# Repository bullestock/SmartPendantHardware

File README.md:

# Devtronic SmartPendant

This project allows controlling a grblHAL based CNC machine without a PC. It also makes work way more convenient.

This fork builds upon the original Devtronic/Nicolai Shlapunov project, which has a store here: https://devtronic.square.site/

I have no intentions to offer this version for sale, but all files are freely available. The changes compared to the original project are:

* Instead of a display with two FCC connectors this version uses a display with a single 2.54 mm pitch connector. This does mean that the pendant is a few millimetres thicker.
* The LEDs have been removed.
* Passives are 0603 instead of 0805.
* Screw terminals have been replaced with JST XH connectors.

# Firmware

Source code for this project can be found here: **https://github.com/bullestock/SmartPendantFirmware**

To load new firmware you can either use OpenOCD, or the [STM32CubeProgrammer](https://www.st.com/en/development-tools/stm32cubeprog.html).

## OpenOCD

For this you need an "ST-Link V2 mini" adapter, which can be obtained for a few dollars from AliExpress and other sites.

Connect the adapter and run this command:

    openocd -f interface/stlink.cfg -f target/stm32f4x.cfg -c "program SmartPendant.elf verify reset exit"

## STM32CubeProgrammer

Connect SmartPendant to PC using USB-C cable. Press and hold BOOT0 button, then short press NRST button, couple seconds later BOOT0 button can be released.
Open STM32CubeProgrammer. In top right corner choose "USB" from drop down list.
If field "Port" in "USB Configuration" show "No DFU detected" click update button near it.
Click "Connect" button - STM32CubeProgrammer should establish connection and show current device memory content.
Click "Open File" in left to corner, select firmware HEX file, then click "Download" button in top left corner.
When flashing is done, close STM32CubeProgrammer and short press NRST button on the Controller to restart it. 

**Note:** if flashing is successful, but firmware isn't work, check STM32CubeProgrammer log. If it says "sector 0000 does not exist" erasing operation wasn't successful and new firmware "merged"(write operation can only flip bits from 1 to 0) with old one. To fix this issue, press "eraser" button in bottom right corner and click "Ok" button in pop up window. After erasing is finished "Device memory" should show only FFFFFFFF. Flash new firmware after that. 

# Parts

To make this project yourself, you will need these essential parts:

* [WeAct BlackPill F411 25M HSE:](https://s.click.aliexpress.com/e/_DC6TlGd)
* [3.5" Display with touchscreen based on ILI9488 LCD controller and FT6236 touch controller](https://www.aliexpress.com/item/1005009339669149.html)
* [60 mm 6 pin 100 PPR handwheel](https://s.click.aliexpress.com/e/_DCFuJHr)
* [SMD connector for display](https://www.aliexpress.com/item/1005005194925318.html) (note that the connector must be aligned with the through holes, and that you need to remove the plastic part of the header on the display; see picture below).
* [Side button switches](https://www.aliexpress.com/item/1005003036287080.html)
* [Front button switches](https://www.aliexpress.com/item/1005007564864690.html)
* [USB C connector](https://www.aliexpress.com/item/1005008913274510.html)
* [Battery holder](https://www.aliexpress.com/item/4000648810345.html)
* [Buzzer](https://www.aliexpress.com/item/32949954569.html)
* The SD card footprint allows for two common sockets to be mounted.
* See the KiCAD files for additional components.

Note the placement of the two display support pieces (glued to the PCB).

Note 8 mm threaded standoff on bottom encoder screw. Two printed spacers are mounted beneath the PCB.

## Case

3D_Print folder of this repo contain 3D files (OpenSCAD and STLs) of the case.

I printed the buttons in TPU filament.

## Dimensions

**160** mm x **65** mm x **24** mm (56 mm with handwheel and handle)

## Schematic

See the kicad directory.

## Firmware

Source code can be found [here](https://github.com/bullestock/SmartPendantFirmware)

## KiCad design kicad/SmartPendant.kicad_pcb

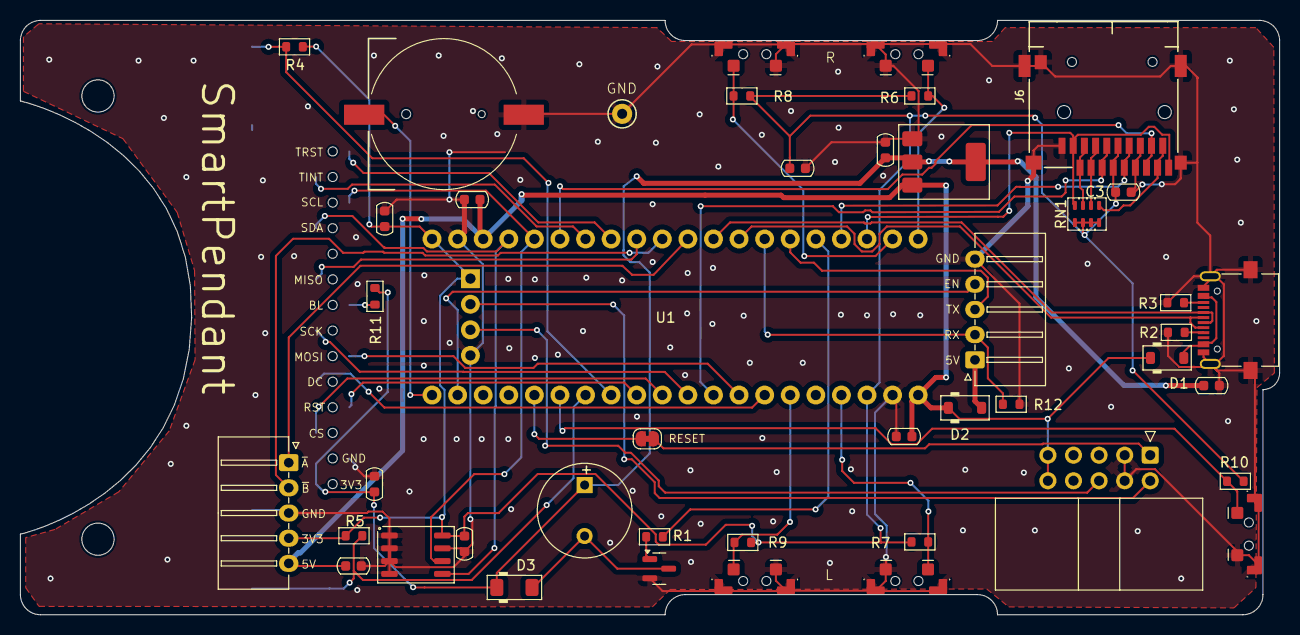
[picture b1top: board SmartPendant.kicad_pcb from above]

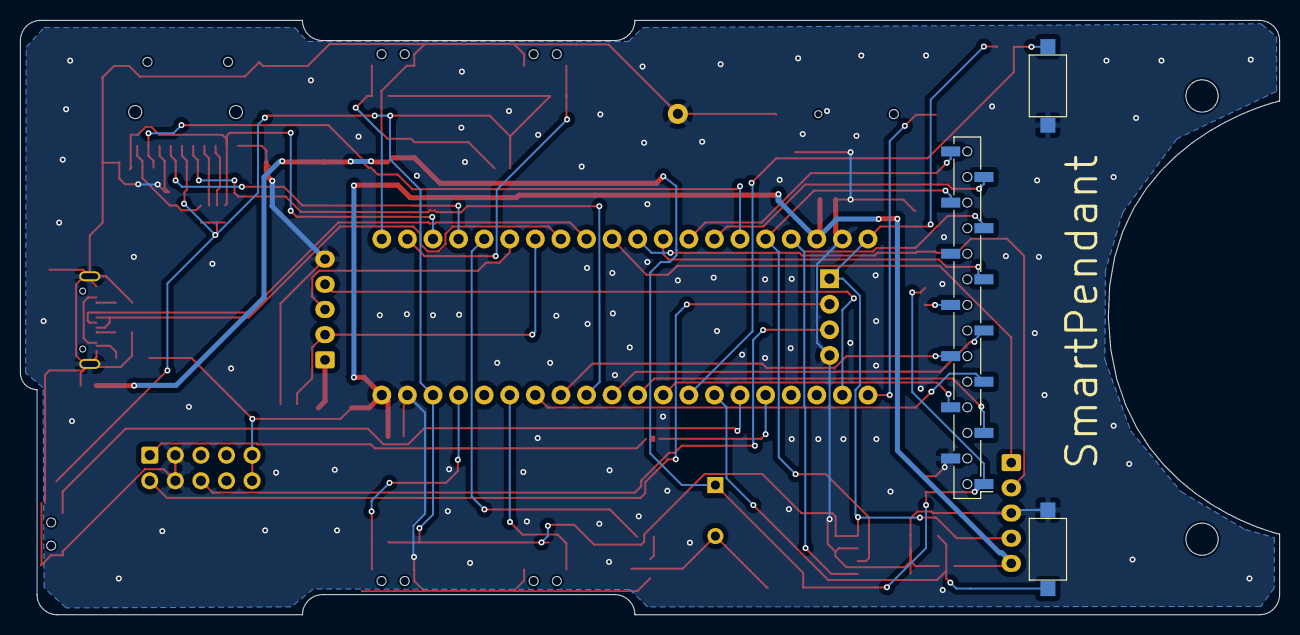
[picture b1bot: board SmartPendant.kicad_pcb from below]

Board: 2 copper layers, 125.0 x 59.0 mm, 49 parts (3 on the bottom side), 48 nets.

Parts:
BT1: CR1220; CR1220_Battery_Holder
BTN_L1: SPST; SW_SPST_CK_RS282G05A3
BTN_LD1: SPST; SMD_Push_Side_button_3x6x3.5mm
BTN_LU1: SPST; SMD_Push_Side_button_3x6x3.5mm
BTN_R1: SPST; SW_SPST_CK_RS282G05A3
BTN_RD1: SPST; SMD_Push_Side_button_3x6x3.5mm
BTN_RU1: SPST; SMD_Push_Side_button_3x6x3.5mm
BTN_USR1: SPST; SMD_Push_Side_button_3x6x3.5mm
BZ1: Buzzer; Buzzer_4.7x9.4mm
C1, C2, C3, C4, C5, C6, C7, C8, C9, C10: 1uF; C_0603_1608Metric
D1, D2: 1N5819; D_SOD-123
D3: 1N4148; D_MiniMELF
H1, H2: MountingHole; MountingHole_3.2mm_M3
J1: UART; JST_XH_S5B-XH-A_1x05_P2.50mm_Horizontal_Compact
J2: ST-LINK; IDC-Header_2x05_P2.54mm_Horizontal
J3: Encoder; JST_XH_S5B-XH-A_1x05_P2.50mm_Horizontal_Compact
J4: Display; PinSocket_1x14_P2.54mm_Vertical_SMD_Pin1Left_TH
J5: USB_C_Receptacle_USB2.0_16P; USB_C_Receptacle_AliExpress_16pin
J6: Micro_SD_Card_Det1; J_SD_Card-micro_dual
Q1: MMBT3904; SOT-23
R1: 470; R_0603_1608Metric
R2, R3: 5k1; R_0603_1608Metric
R4, R5, R6, R7, R8, R9, R10: 1kΩ; R_0603_1608Metric
R11: 0; R_0603_1608Metric
R12: 10kΩ; R_0603_1608Metric
RN1: 10k; R_Array_Concave_4x0603
RST1: SB_402; SolderJumper-2_P1.3mm_Bridged_RoundedPad1.0x1.5mm
TP1: GND; TestPoint_Keystone_5000-5004_Miniature
U1: WEACT BLACKPILL F4X1; BlackPill_STLINK
U2: AMS1117-3.3; SOT-223-3_TabPin2
U3: MB85RC256VPNF-G-JNERE1; SOP-8_3.9x4.9mm_P1.27mm

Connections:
+3.3V: BZ1.1 (+), C6.1, C7.1, C8.1, D3.1 (K), J4.1, R11.1, U2.2 (VO)
+5V: C2.1, C9.1, C10.1, D1.1 (K), D2.1 (K), J2.9, J2.10, J3.5, U1.18 (5V), U1.40 (5V), U2.3 (VI)
BAT: BT1.1 (+), U1.21 (VBAT)
BTN_LD: BTN_RD1.1, R9.2, U1.35 (PB1)
BTN_LU: BTN_RU1.2, R7.2, U1.37 (PB10)
BTN_RD: BTN_LD1.2, R8.2, U1.2 (PB13)
BTN_RU: BTN_LU1.1, R6.2, U1.1 (PB12)
BUZZER: R1.1, U1.5 (PA8)
ENC_A: J3.1, U1.10 (PA15)
ENC_B: J3.2, U1.11 (PB3)
GND: BT1.2 (-), BTN_L1.2, BTN_LD1.1, BTN_LD1.SH (B), BTN_LU1.2, BTN_LU1.SH (B), BTN_R1.2, BTN_RD1.2, BTN_RD1.SH (B), BTN_RU1.1, BTN_RU1.SH (B), BTN_USR1.1, BTN_USR1.SH (B), C1.2, C2.2, C3.2, C4.2, C5.2, C6.2, C7.2, C8.2, C9.2, C10.2, J1.5, J2.3, J2.4, J3.3, J4.2, J5.A1 (GND), J5.A12 (GND), J5.B1 (GND), J5.B12 (GND), J5.S1 (SHIELD), J6.6 (VSS), J6.10 (SHIELD), Q1.2 (E), R2.2, R3.2, R12.2, TP1.1, U1.19 (GND), U1.39 (GND), U1.44 (GND), U2.1 (GND), U3.1 (A0), U3.2 (A1), U3.3 (A2), U3.4 (VSS), U3.7 (WP)
LCD_CS: J4.3, U1.30 (PA4)
LCD_DC: J4.5, U1.34 (PB0)
LCD_MISO: J4.9, U1.12 (PB4)
LCD_MOSI: J4.6, U1.33 (PA7)
LCD_RST: J4.4, U1.29 (PA3)
LCD_SCK: J4.7, U1.31 (PA5)
LEFT_BTN: BTN_R1.1, R5.2, U1.27 (PA1)
MPG_EN: J1.4, U1.22 (PC13)
unnamed: BZ1.2 (-), D3.2 (A), Q1.3 (C)
unnamed: D1.2 (A), J5.A4 (VBUS), J5.A9 (VBUS), J5.B4 (VBUS), J5.B9 (VBUS)
unnamed: D2.2 (A), J1.1
unnamed: J2.1, RST1.2 (B)
unnamed: J4.8, R11.2
unnamed: J5.A5 (CC1), R2.1
unnamed: J5.B5 (CC2), R3.1
unnamed: J6.8 (DAT1), RN1.5 (R4.2)
unnamed: J6.1 (DAT2), RN1.7 (R2.2)
unnamed: J6.2 (DAT3/CD), RN1.6 (R3.2)
unnamed: Q1.1 (B), R1.2
RIGHT_BTN: BTN_L1.1, R4.2, U1.28 (PA2)
RST: RST1.1 (A), U1.25 (~RESET)
SCL: J4.12, U1.16 (PB8), U3.6 (SCL)
SDA: J4.11, U1.17 (PB9), U3.5 (SDA)
SDIO_CD: J6.9 (DET), RN1.8 (R1.2), U1.3 (PB14)
SDIO_CK: J6.5 (CLK), U1.4 (PB15)
SDIO_CMD: J6.3 (CMD), U1.32 (PA6)
SDIO_D0: J6.7 (DAT0), U1.15 (PB7)
SWCLK: J2.6, U1.43 (SWSCK)
SWDIO: J2.2, U1.42 (SWDIO)
TOUCH_INT: J4.13, U1.14 (PB6)
TOUCH_RST: J4.14, U1.13 (PB5)
UART_RX: J1.2, R12.1, U1.7 (PA10)
UART_TX: J1.3, U1.6 (PA9)
USB_DN: J5.A7 (D-), J5.B7 (D-), U1.8 (PA11)
USB_DP: J5.A6 (D+), J5.B6 (D+), U1.9 (PA12)
USR_BTN: BTN_USR1.2, R10.2, U1.26 (PA0)
VCC: C1.1, C3.1, C4.1, C5.1, J3.4, J6.4 (VDD), R4.1, R5.1, R6.1, R7.1, R8.1, R9.1, R10.1, RN1.1 (R1.1), RN1.2 (R2.1), RN1.3 (R3.1), RN1.4 (R4.1), U1.20 (3V3), U1.38 (3V3), U1.41 (3.3V), U3.8 (VDD)

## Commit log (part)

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2025-05-31 Fix spelling errors.
2025-05-31 Add raw import from EasyEDA.
2025-05-31 Fix cosmetics.
2025-05-31 Update schematic to match V1.3.
2025-05-31 Add footprints.
2025-06-23 Make side switch footprint.
2025-06-30 Tweak.
2025-07-16 Do not generate raft.
2025-07-16 Remove last traces of raft nonsense.
2025-07-16 More cleanup, adapt to new display.
2025-07-17 Fix encoder screw hole.
2025-07-17 Make room for display, remove LED holes.
2025-07-17 Remove LEDs.
2025-07-17 Fix bottom.
2025-07-18 Fix bottom display support.
2025-07-18 Remove unnecessary bottom button.
2025-07-18 Add new display connector.
2025-07-30 Change most symbols to proper KiCad ones.
2025-07-30 Update rest of power symbols.
2025-07-30 Fix display hole size and position.
2025-07-30 Add footprints, initial outline.
2025-08-01 Fix some footprint issues.
2025-08-02 Update BlackPill footprint.
2025-08-02 Fix some component positions.
2025-08-02 Move components around.
2025-08-02 Fix ERC violations.
2025-08-02 Use angle JST connectors.
2025-08-02 Optimize component placement.
2025-08-03 Tweak layout.
2025-08-04 Adjust display height.
2025-08-04 Remove generated file.
2025-08-04 Increase heigth again.
2025-08-04 Try to fix front button holes.
2025-08-04 Add PCB supports.
2025-08-04 Spelling.
2025-08-04 Adjust size.
2025-08-04 Add PCB support.
2025-08-04 Fix positioning issues.
2025-08-04 Fix DRC error.
2025-08-04 Set provisional footprint for buzzer.
2025-08-04 Enlarge front button holes.
2025-08-05 Make front buttons fit holes.
2025-08-05 Fix bottom button holes position.
2025-08-05 Fix lock height.
2025-08-05 Fix outline.
2025-08-08 More button tweaks.
2025-08-08 Make PCB wider.
2025-08-09 Increase height.
2025-08-09 Change front buttons.
2025-08-09 Adapt height for new tactile button.
2025-08-09 Add 10 mm standoff on encoder screw.
2025-08-15 Correct last footprints.
2025-08-15 Start routing.
2025-08-15 Adjust skirt height.
2025-08-15 Fix bottom standoff height.
2025-08-15 Route some more.
2025-08-16 More routing.
2025-08-16 Complete routing.
2025-08-16 Add ground planes.
2025-08-16 Adjust silk screen.
2025-09-13 Fix orientation of display connector.
2025-09-14 Add GND test point.
2025-09-14 Add labels.
2025-09-14 Invert A, B.
2025-09-18 Use resistor array; make references consecutive.
2025-09-19 Optimize SD card footprint and routing.
2025-09-20 Add dual footprint for SD-card socket.
2025-09-22 Use dual SD-card footprint.
2025-10-05 Increase width of power tracks, add stitching vias.
2025-10-18 Add stencil.
2025-10-23 Remove unneeded pads.
2025-10-25 Add missing SD card pad. Swap left/right side buttons.
2025-10-25 Swap left and right front buttons.
2025-10-25 Move buzzer inwards.
2025-10-26 Add spacers; tweak case.
2025-10-26 Add new pictures.
2025-10-27 Move top switch.
2025-10-27 Fix length.
2025-10-27 Fix skirt size.
2025-10-27 Make buttons move again, oops.
2025-10-27 Add links to new parts, describe differences.
2025-10-27 Crop picture; add PCB side supports.
2025-10-27 Add picture and note about display.
2025-10-27 Add inside photo.
2025-10-28 Increase height slightly.
2025-10-28 Fix lock size.
2025-11-01 Revert "Increase height slightly."
    This reverts commit 1170e3b782fb1b672919bf61e8fbac57eba1ba4c.
2025-11-01 Adjust lock sizes.
2025-11-02 Update picture.
2025-11-02 Fix extension.
2025-11-15 Add display labels.
